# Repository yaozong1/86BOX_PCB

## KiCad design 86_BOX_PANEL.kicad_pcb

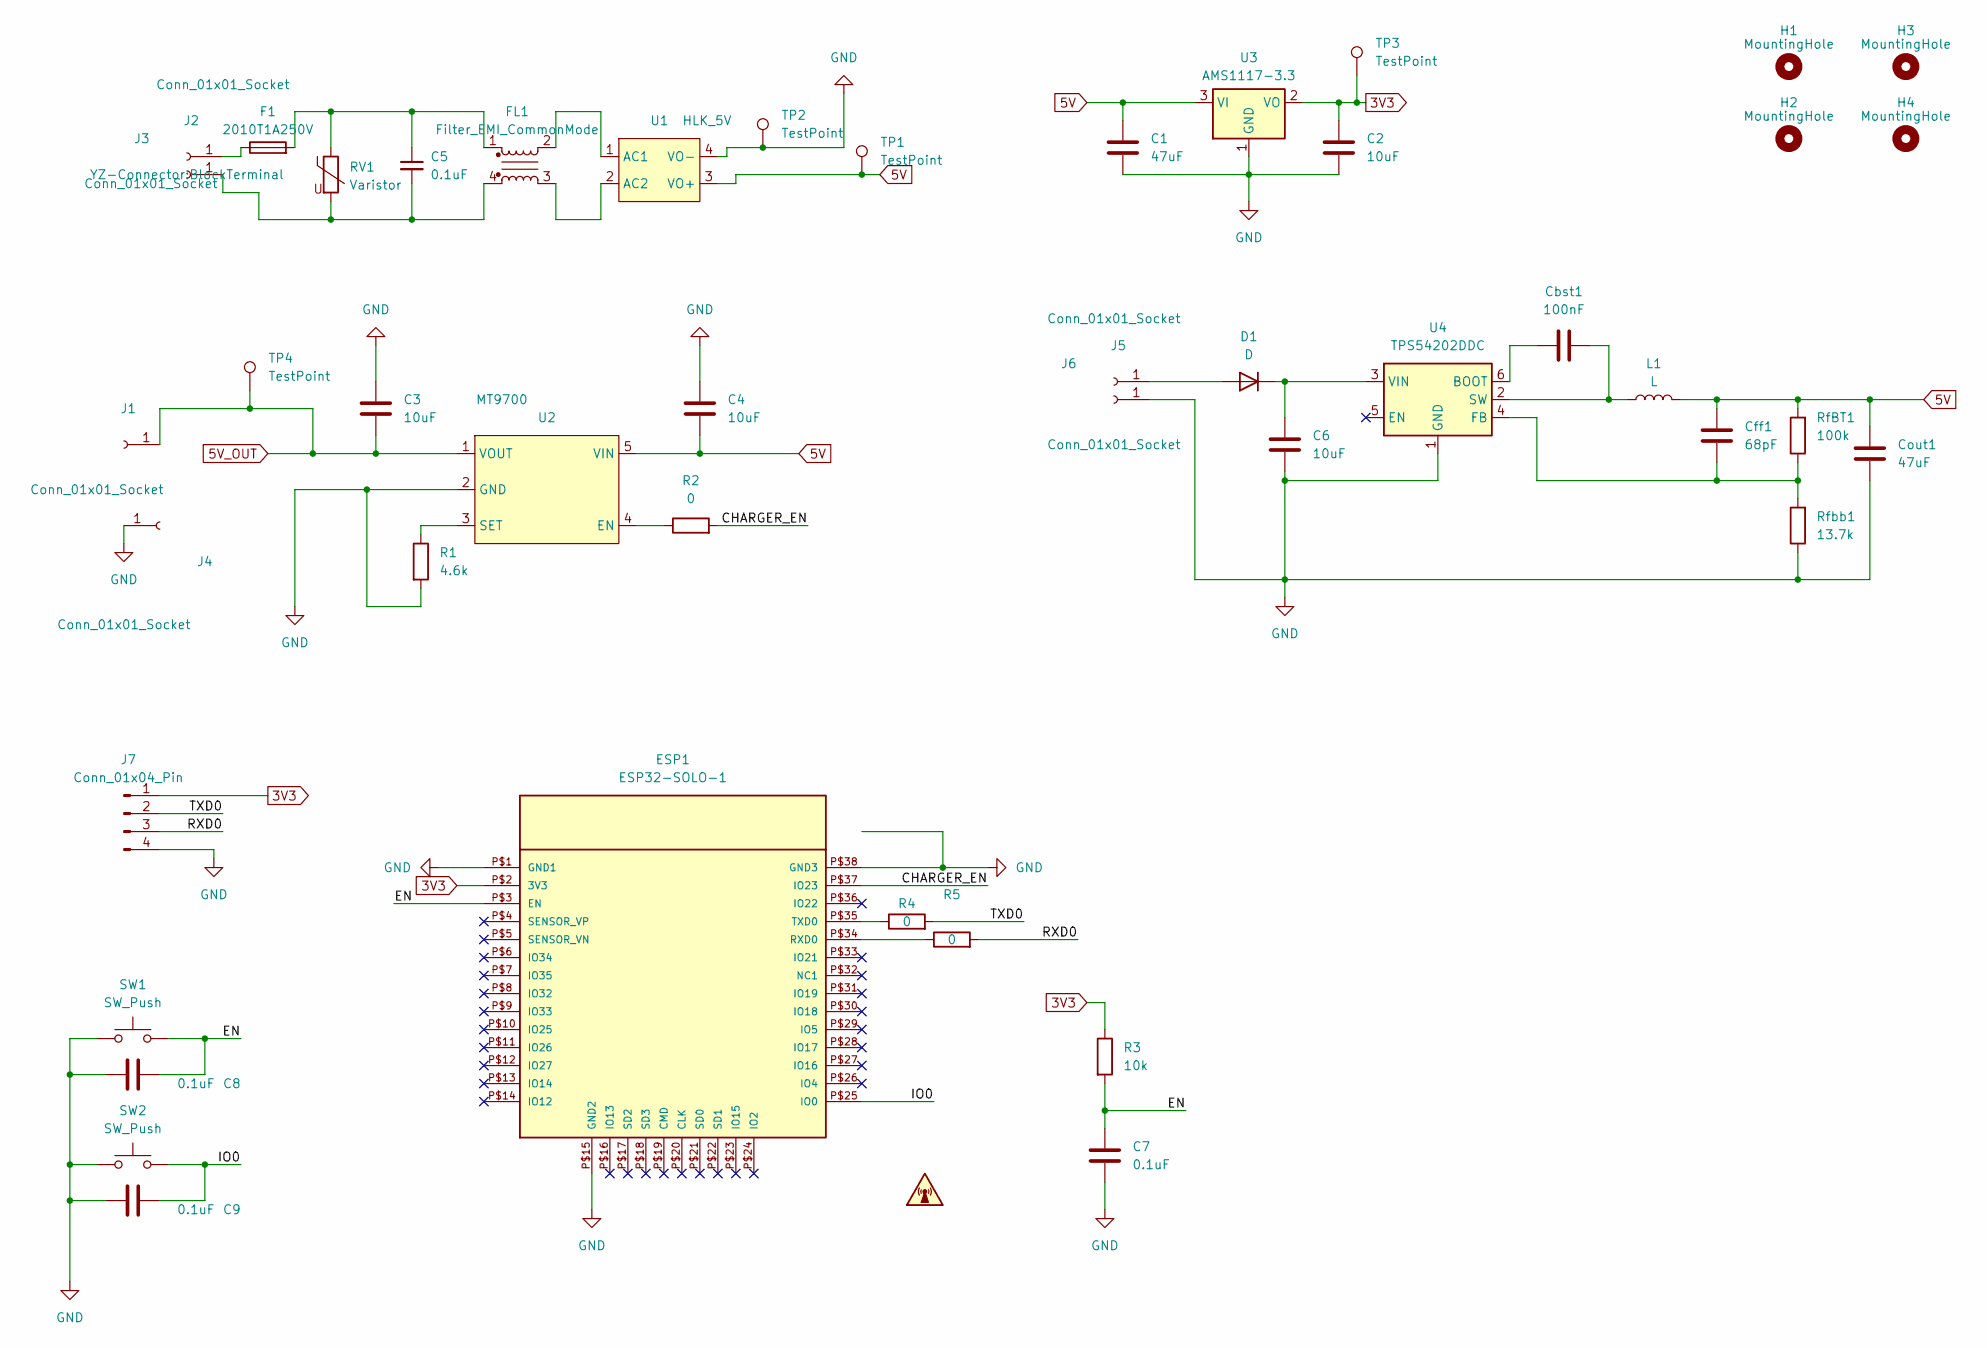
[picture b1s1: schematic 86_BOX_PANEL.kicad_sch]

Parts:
C1: 47uF; C_0805_2012Metric; MPN GRM21BR61A476ME15L
C2, C3, C4, C6: 10uF; C_0805_2012Metric; MPN GRM21BR61H106KE43L
C5: 0.1uF; C_Rect_L11.0mm_W4.2mm_P10.00mm_MKT; MPN PX104K2C1008
C7, C8, C9: 0.1uF; C_0603_1608Metric_Pad1.08x0.95mm_HandSolder; MPN GRM188R71H104KA93D
Cbst1: 100nF; C_0402_1005Metric_Pad0.74x0.62mm_HandSolder; MPN GRM155R71H104KE14D
Cff1: 68pF; C_0402_1005Metric_Pad0.74x0.62mm_HandSolder; MPN GRM1555C1H680JA01D//
Cout1: 47uF; C_1210_3225Metric_Pad1.33x2.70mm_HandSolder; MPN GRM32ER61C476KE15L
D1: D; D_SMA_Handsoldering; MPN SS34
ESP1: ESP32-SOLO-1; MPN ESP32-SOLO-1
F1: 2010T1A250V; Fuse_Littelfuse_395Series; MPN 2010T1A250V
FL1: Filter_EMI_CommonMode; UU9.8; MPN UU9.8-10mH,插件
H1, H2, H4: MountingHole; MountingHole_2.2mm_M2_Pad_Via; MPN DNP
H3: MountingHole; MountingHole_2.2mm_M2_ISO14580; MPN DNP
J1, J4: Conn_01x01_Socket; springNeedle
J2, J3, J5, J6: Conn_01x01_Socket; BlockTerminal
J7: Conn_01x04_Pin; PinHeader_1x04_P1.27mm_Vertical
L1: L; L_Bourns_SRP7028A_7.3x6.6mm; MPN 74437349150//
R1: 4.6k; R_0603_1608Metric_Pad0.98x0.95mm_HandSolder; MPN FRC0805F4601TS
R2, R4, R5: 0; R_0603_1608Metric_Pad0.98x0.95mm_HandSolder; MPN 0603WAF0000T5E
R3: 10k; R_0603_1608Metric_Pad0.98x0.95mm_HandSolder; MPN 0603WAF1002T5E
RV1: Varistor; RV_Disc_D12mm_W6.1mm_P7.5mm; MPN 10D561K
RfBT1: 100k; R_0402_1005Metric_Pad0.72x0.64mm_HandSolder; MPN CRCW0402100KFKED
Rfbb1: 13.7k; R_0402_1005Metric_Pad0.72x0.64mm_HandSolder; MPN CRCW040213K7FKED
SW1, SW2: SW_Push; SW_Push_SPST_NO_Alps_SKRK; MPN TS-1088-AR02016
TP1, TP2, TP3, TP4: TestPoint; TestPoint_Pad_D1.5mm
U1: HLK_5V; HLK-10M05; MPN HLK_5V
U2: MT9700; SOT-23-5_HandSoldering; MPN MT9700
U3: AMS1117-3.3; SOT-223-3_TabPin2; MPN AMS1117-3.3
U4: TPS54202DDC; SOT-23-6; MPN TPS54202DDCR

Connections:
3V3: C2.1, ESP1.P$2 (3V3), J7.1, R3.1, TP3.1, U3.2 (VO)
5V: C1.1, C4.2, Cff1.1, Cout1.1, L1.2, RfBT1.2, TP1.1, U1.3 (VO+), U2.5 (VIN), U3.3 (VI)
5V_OUT: C3.2, J1.1, TP4.1, U2.1 (VOUT)
/CHARGER_EN: ESP1.P$37 (IO23), R2.2
/EN: C7.1, C8.2, ESP1.P$3 (EN), R3.2, SW1.2
/IO0: C9.2, ESP1.P$25 (IO0), SW2.2
/RXD0: J7.3, R5.2
/TXD0: J7.2, R4.2
GND: C1.2, C2.2, C3.1, C4.1, C6.2, C7.2, C8.1, C9.1, Cout1.2, ESP1.P$1 (GND1), ESP1.P$15 (GND2), ESP1.P$38 (GND3), J4.1, J6.1, J7.4, R1.2, Rfbb1.1, SW1.1, SW2.1, TP2.1, U1.4 (VO-), U2.2 (GND), U3.1 (GND), U4.1 (GND)
unnamed: C5.1, F1.2, FL1.1, RV1.1
unnamed: D1.2 (A), J5.1
unnamed: C6.1, D1.1 (K), U4.3 (VIN)
unnamed: ESP1.P$34 (RXD0), R5.1
unnamed: ESP1.P$35 (TXD0), R4.1
unnamed: F1.1, J2.1
unnamed: C5.2, FL1.4, J3.1, RV1.2
unnamed: FL1.2, U1.1 (AC1)
unnamed: FL1.3, U1.2 (AC2)
unnamed: R2.1, U2.4 (EN)
unnamed: R1.1, U2.3 (SET)
unnamed: Cbst1.1, U4.6 (BOOT)
unnamed: Cff1.2, RfBT1.1, Rfbb1.2, U4.4 (FB)
unnamed: Cbst1.2, L1.1, U4.2 (SW)

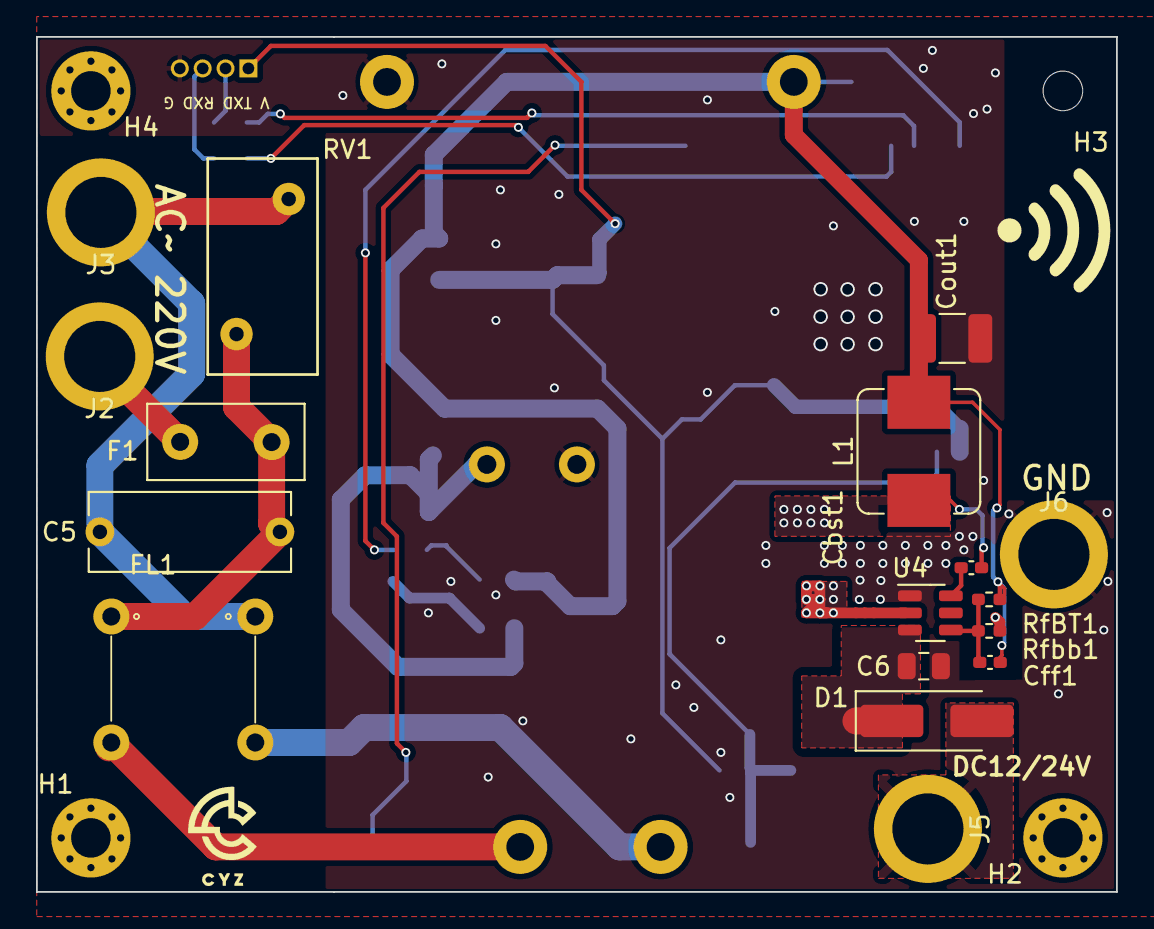
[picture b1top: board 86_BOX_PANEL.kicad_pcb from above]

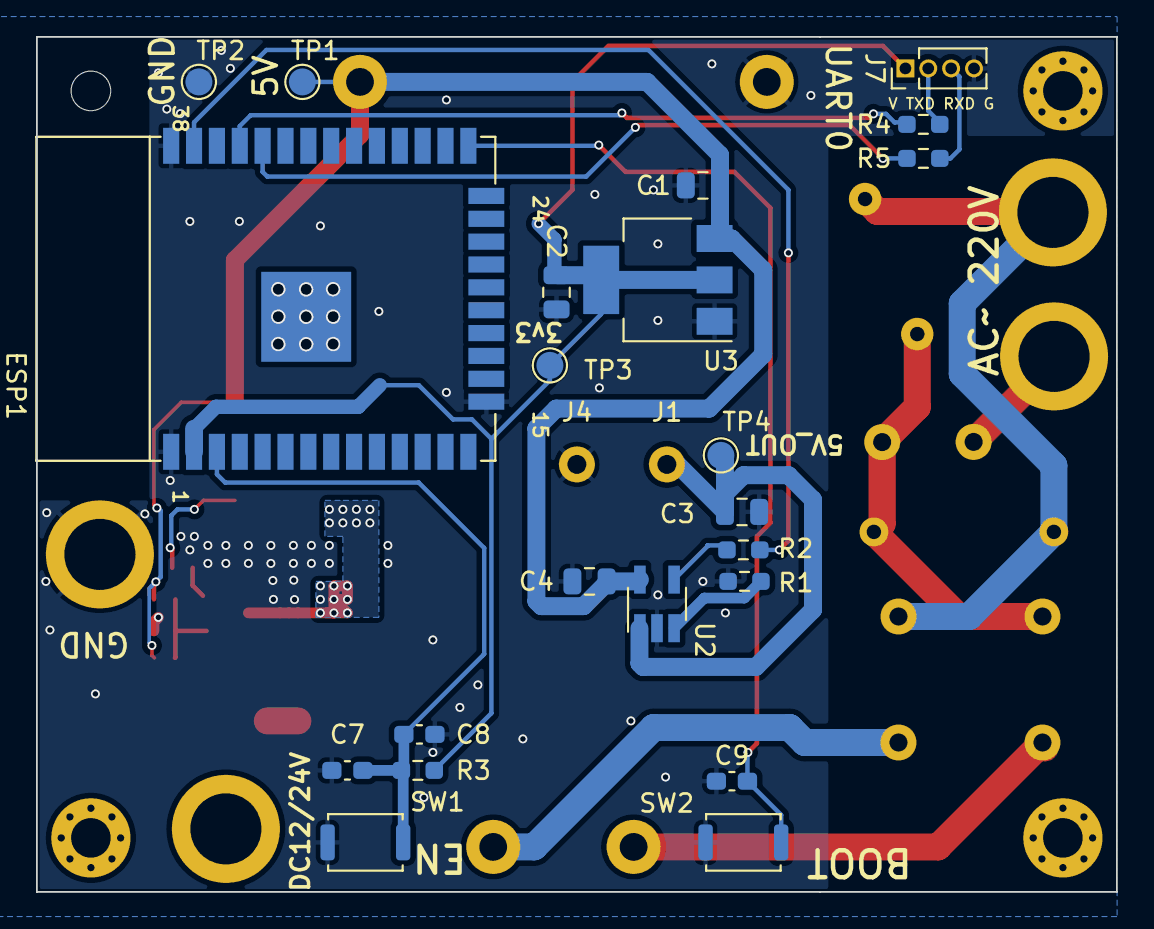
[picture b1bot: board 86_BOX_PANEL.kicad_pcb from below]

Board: 2 copper layers, 60.0 x 47.5 mm, 46 parts (24 on the bottom side), 23 nets.

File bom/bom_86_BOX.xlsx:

| References | Value | Footprint | Description | MPN | Quantity
1 | C2, C3, C4 | 10uF | C_0805_2012Metric | CAP CER 10UF 10V X5R 0805 |  | 3
2 | C7, C8, C9 | 0.1uF | C_0603_1608Metric_Pad1.08x0.95mm_HandSolder | CAP CER 0.1UF 10V X7R 0603 |  | 3
3 | C1 | 47uF | C_0805_2012Metric | CAP CER 47UF 10V X5R 0805 |  | 1
4 | C5 | 0.1uF | C_Rect_L11.0mm_W4.2mm_P10.00mm_MKT | 安规电容 |  | 1
5 | C6 | 10uF | C_0805_2012Metric | CAP CER 10UF 50V X5R 0805 | CL32A106KBJNNNE | 1
6 | R4, R5 | 0 | R_0603_1608Metric_Pad0.98x0.95mm_HandSolder | RES SMD 0 OHM 1% 1/16W 0603 |  | 2
7 | R1 | 4.6k | R_0603_1608Metric_Pad0.98x0.95mm_HandSolder | RES SMD 4.6k OHM 1% 1/16W 0603 |  | 1
8 | R2 | 1k | R_0603_1608Metric_Pad0.98x0.95mm_HandSolder | RES SMD 1k OHM 1% 1/16W 0603 |  | 1
9 | R3 | 10k | R_0603_1608Metric_Pad0.98x0.95mm_HandSolder | RES SMD 10k OHM 1% 1/16W 0603 |  | 1
10 | L1 | L | L_Bourns_SRP7028A_7.3x6.6mm | FIXED IND 15UH 2.75A 92 MOHM SMD | 74437349150// | 1
11 | D1 | D | D_SMA_Handsoldering | DIODE SCHOTTKY 40V 3A SMA | SS34 | 1
12 | U1 | HLK_5V | HLK-10M05 | HILINK 220V_5V |  | 1
13 | U2 | MT7900 | SOT-23-5_HandSoldering |  |  | 1
14 | U3 | AMS1117-3.3 | SOT-223-3_TabPin2 |  |  | 1
15 | U4 | TPS54202DDC | SOT-23-6 |  | TPS54202DDC | 1
16 | F1 | 2010T1A250V | Fuse_Littelfuse_395Series |  | 2010T1A250V | 1
17 | SW1, SW2 | SW_Push | SW_Push_SPST_NO_Alps_SKRK |  |  | 2
19 | Cbst1 | 100nF | C_0402_1005Metric_Pad0.74x0.62mm_HandSolder | CAP CER 0.1UF 50V X5R 0402 | C1005X5R1H104K050BB// | 1
20 | Cff1 | 68pF | C_0402_1005Metric_Pad0.74x0.62mm_HandSolder | CAP CER 56PF 50V C0G/NP0 0402 | GRM1555C1H560JA01D// | 1
21 | Cout1 | 47uF | C_1210_3225Metric_Pad1.33x2.70mm_HandSolder | CAP CER 47UF 16V X5R 1210 | GRM32ER61C476KE15L | 1
22 | ESP1 | ESP32-SOLO-1 | ESP32-SOLO-1 | Bluetooth, WiFi 802.11b/g/n, Bluetooth v4.2 +EDR, Class 1, 2 and 3 Transceiver 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 |  | 1
23 | FL1 | Filter_EMI_CommonMode | UU9.8 |  |  | 1
24 | Rfbb1 | 13.7k | R_0402_1005Metric_Pad0.72x0.64mm_HandSolder | RES SMD 13.7K OHM 1% 1/16W 0402 | CRCW040213K7FKED | 1
25 | RfBT1 | 100k | R_0402_1005Metric_Pad0.72x0.64mm_HandSolder | RES SMD 100K OHM 1% 1/16W 0402 | CRCW0402100KFKED | 1
26 | RV1 | Varistor | RV_Disc_D12mm_W6.1mm_P7.5mm | 压敏电阻 |  | 1
27 | J2, J3, J5, J6 | Conn_01x01_Socket | BlockTerminal |  |  | 4
28 | J1, J4 | Conn_01x01_Socket | spring_Needle |  |  | 2

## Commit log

2023-12-19 first
